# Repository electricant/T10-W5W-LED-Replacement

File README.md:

# T10-W5W-LED-Replacement

KiCad design for a T10 (W5W) 12V bulb replacement using LEDs, reducing power consumption and providing a longer lifespan compared to traditional filament bulbs.

## Overview

The goal is to create a more energy-efficient, long-lasting LED alternative to traditional filament bulbs commonly used in automotive applications.

The LEDs are driven by the LT1962 voltage regulator, acting as a constant current source for stable LED operation.
The LT1962 is a low-dropout (LDO) linear voltage regulator with the following key features that make it particularly suitable for this application:
- **Low Dropout Voltage:** The LT1962 has an exceptionally low dropout voltage (typically 270mV at 300mA), making it ideal for automotive environments where the input voltage can fluctuate.
- **High Input Voltage Range:** With an input voltage range of up to 20V, the LT1962 can easily handle the variations in automotive electrical systems, which typically range (roughly) from 11 to 14V
- **Thermal Protection:** Built-in thermal shutdown protects the regulator and the LED circuit from overheating, enhancing the overall reliability.

A series resistor (R3 in the schematic) is used to set the current flowing through the LEDs in conjunction with the LT1962 voltage regulator.
The LT1962 regulates the voltage to a specific reference value (1.22V for the adjustable version, or fixed values such as 1.5V, 1.8V, etc., depending on the version used).

The value of the series resistor $R_3$ can be calculated using the following formula:

$$
R_3 = \frac{V_{ref}}{I_{LED}}
$$

Where:
- $V_{ref}$ is the reference voltage of the LT1962 (e.g., 1.22V for the adjustable version).
- $I_{LED}$ is the desired current through the LED.

It's important to ensure that the total voltage drop across the LED and the resistor remains below 12V to maintain constant current operation. If the LED's forward voltage is too high, or if the input voltage is too low, the LT1962 might not regulate properly, leading to variations in the LED current.

### Example Calculation

If you are using the adjustable version of the LT1962 with a reference voltage $V_{ref}$ of 1.22V and you want to set the LED current $I_{LED}$ to 20mA, the resistor value would be:

$$
R_3 = \frac{1.22V}{0.02A} = 61 \Omega
$$

Rounded to the nearest standard value, you would use a **62Ω** resistor to achieve approximately a 19.7mA current through the LED.

## Contributions

Contributions are welcome! Feel free to fork this repository and submit a pull request with your improvements.

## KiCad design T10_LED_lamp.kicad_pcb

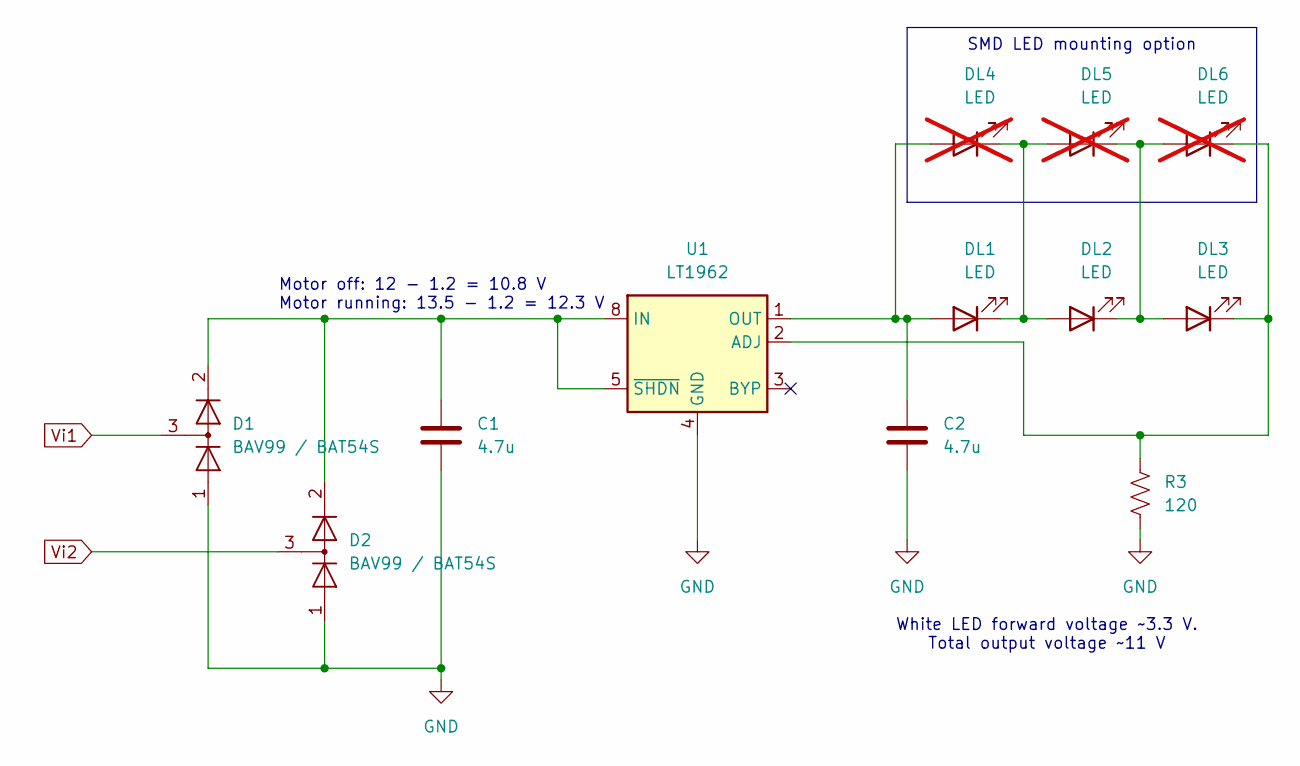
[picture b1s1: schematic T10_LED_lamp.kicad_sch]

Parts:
C1, C2: 4.7u; C_0805_2012Metric
D1, D2: BAV99 / BAT54S; SOT-23_Handsoldering
DL1, DL2, DL3: LED; LED_D5.0mm_Clear
DL4, DL5, DL6: LED; LED_PLCC-2_3.4x3.0mm_KA; not fitted
R3: 120; R_0805_2012Metric_Pad1.20x1.40mm_HandSolder
U1: LT1962; MSOP-8_3x3mm_P0.65mm

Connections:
GND: C1.2, C2.2, D1.1 (K), D2.1 (K), R3.1, U1.4 (GND)
unnamed: C1.1, D1.2 (A), D2.2 (A), U1.5 (~SHDN), U1.8 (IN)
unnamed: C2.1, DL1.2 (A), DL4.2 (A), U1.1 (OUT)
unnamed: DL1.1 (K), DL2.2 (A), DL4.1 (K), DL5.2 (A)
unnamed: DL2.1 (K), DL3.2 (A), DL5.1 (K), DL6.2 (A)
unnamed: DL3.1 (K), DL6.1 (K), R3.2, U1.2 (ADJ)
Vi1: D1.3 (K)
Vi2: D2.3 (K)

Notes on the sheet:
SMD LED mounting option
Motor off: 12 - 1.2 = 10.8 V Motor running: 13.5 - 1.2 = 12.3 V
White LED forward voltage ~3.3 V. Total output voltage ~11 V

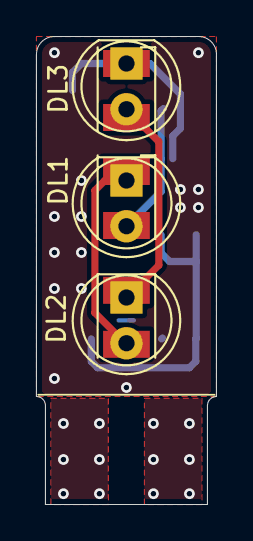
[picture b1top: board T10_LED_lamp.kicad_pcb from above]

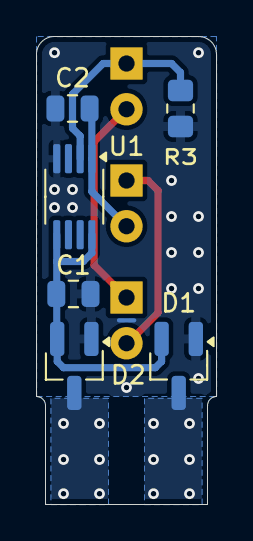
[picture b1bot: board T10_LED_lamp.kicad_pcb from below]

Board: 2 copper layers, 10.0 x 26.0 mm, 12 parts (6 on the bottom side), 6 nets.

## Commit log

2024-08-13 Add design files and images
